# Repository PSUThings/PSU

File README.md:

Both designs work without issue on my end, BOM and Gerbers are there along with Eagle files.  
I have included as much info as i think you will need to get one of these up and running without issue.   
The rear adapters are stl files ready for 3d printing, the original design files i couldnt find, but shouldnt be needed.  
No licence, do what you want with the files.   

As suggested by someone, here is the links to oshpark. These should be easier for people who have no idea how to get a pcb made but can solder well. 

DreamPSU
https://oshpark.com/shared_projects/REVINxcE

SaturnPSU
https://oshpark.com/shared_projects/gURypobA

<!-- Now i have that out the way. Here is a little rant for you that checked this file. This shit is what represents just under 2 years of my life, I loved making the Dreamcast version of the psu cause it was new, fun and interesting, i learned so much from doing this, from eagle stuff to taking a labor of love to production and seeing peoples feedback. But the saturn version? I dont think there was one part of the experience that i enjoyed. Which sucks, i really wanted to do the saturn version cause of peoples constant asking for it, emails, tweets, facebook messages, all the time, so i was totally down to do it. But my god what a fucking shit show its turned out to be. From the mess that is saturn revisions to the fucking absolute disgrace that was the indiegogo campaign. There are god knows how many saturn revisions, which i had to try and source hardware for, which by the way is not an easy feat when your relying on ebay pictures to try and work out if you already own that version of the console, let alone the price of those things, most of which i brought non working or "untested", they cost me between £20-30 each, and i have no use for them after the final design was done. I dont play the saturn and when i did play it as a kid i wasnt a fan of it to be honest. My love was always the PS1 and the dreamcast. The fuck fest that happened with the campaign was nothing but a nightmare, from the first time the manafacturer screwed me over by increasing a quote by almost 30%, to issues with the cabling design for the top doown saturns and chinas inability to follow basic instructions, to the issues with fake or cloned TI chips. i couldnt beleive it. When i was oriignaly considering the saturn and wether or not i should go ahead and do a campaign for it (which by the way i had to, i know people are like "well what about the money you made from the dreampsu campaign", that dreampsu campaign left me damn near 2k in debt. so there was no money to put towards the saturn stuff besides a few intiial prototypes) i never would have dreamed it would turn out the way it did. I let myself down, everyone who help with the campaign down and everyone who made an order elsewhere down. That shit is not easy to handle when your as mentally fucked as i am lmao. And if your wondering, i dont care if i come across as weird or fucked up here, im drunk and im tired and pissed off, let me rant. Talking of ranting, its SOOOO hard to be nice to people all the time when they are berating you and trying to make you feel like shit (which btw guys, good luck cause i already feel as shit as its humanily possible), I do not envy people in customer service jobs.  OK im probably gonna leave this now before i start rambling, but i will say this, to anyone who has a neat idea or something that will help out the retro community, run at it with full force, make it the best thing you can possibly make it and then for the love of god dont try to sell it to anyone. Release that shit open source and never have to go though the same shit i have with this. I do want to say, once again to everyone that backed this thing, i am sorry from the bottom of my heart, this shit rips me apart every damn day knowing that you guys didnt get what u wanted. Hell i fear checking my phone or emails anytime it makes a noise though fear i have to face one of you again. I would also like to say thank you to everyone that was understanding of the sitation, everyone who offered help or guidance and advice, i cannot thank you enough, i dont want to mention people by names cause that aint fair, but you know who you are, even i replied to your email with not very much in the way of words, or didnt reply at all, i read every single email and bit of adcive you sent and i thank you for that.   Thats it from be folks, If at any point i decide to do another PSU for another console, i wont be selling them in any way shape or form, but i will make the files avaible for people as a further apology to everyone for all that has happened.  -->

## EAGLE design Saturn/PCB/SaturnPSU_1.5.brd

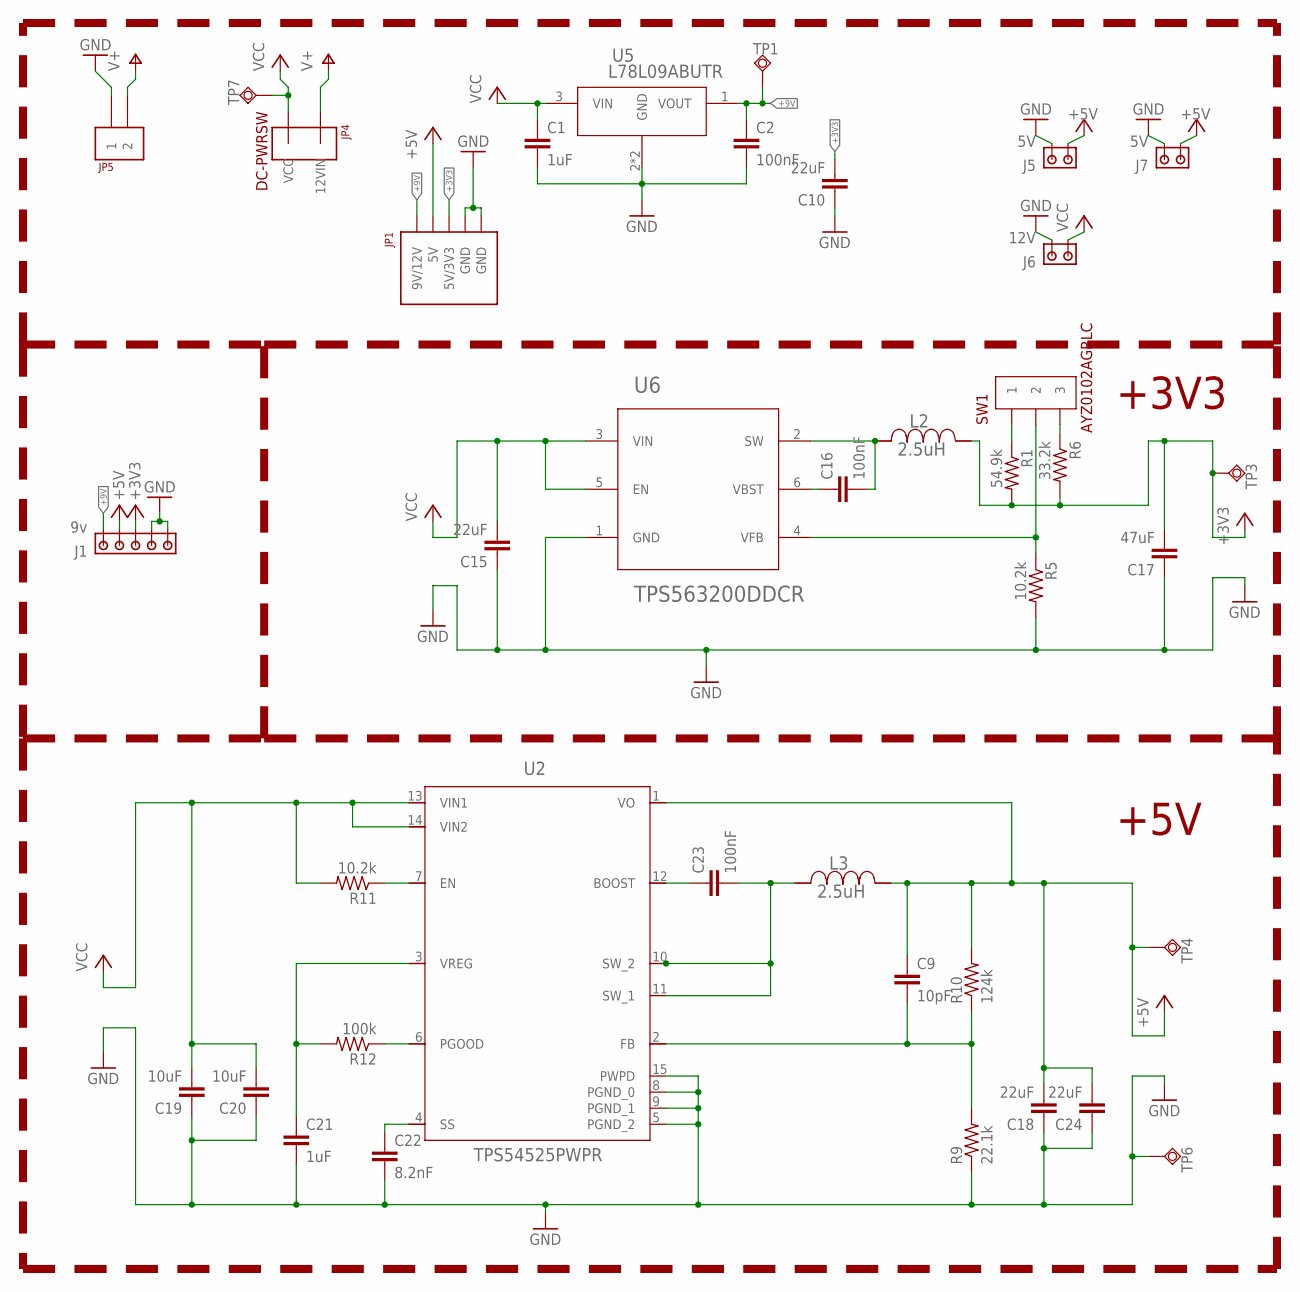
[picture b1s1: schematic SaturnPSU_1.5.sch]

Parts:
C1, C21: 1uF; C0603
C2, C16, C23: 100nF; C0603
C9: 10pF; C0603
C10, C15, C18, C24: 22uF; C0805
C17: 47uF; C1206
C19, C20: 10uF; C1206
C22: 8.2nF; C0603
J1: 9v; KF2510-5A-2.54MM
J5, J7: 5V; 6030916A
J6: 12V; 6030916A
JP1: MOLEX-5PIN-09-48-3054; 09-48-3054
JP4: DC-PWRSW; 1-1123724-2
JP5: 640445-2_3.96MM-2PIN-HEADER
L2, L3: 2.5uH; PA4341.252NLT
R1: 54.9k; R0603
R5, R11: 10.2k; R0603
R6: 33.2k; R0603
R9: 22.1k; R0603
R10: 124k; R0603
R12: 100k; R0603
SW1: AYZ0102AGRLC
TP1, TP3, TP4, TP6, TP7: TPSQB1,27; B1,27
U2: TPS54525PWPR; R-PDSO-G14
U5: L78L09ABUTR; SOT-89
U6: TPS563200DDCR; DDC0006A

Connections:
2: C23.2, L3.P$1 (1), U2.10 (SW_2), U2.11 (SW_1)
+3V3: C10.2, C17.2, J1.3, JP1.3 (5V/3V3), L2.P$2 (2), R1.2, R6.2, TP3.TP
+5V: C9.1, C18.2, C24.2, J1.4, J5.POWER, J7.POWER, JP1.4 (5V), L3.P$2 (2), R10.2, TP4.TP, U2.1 (VO)
+9V: C2.1, J1.5, JP1.5 (9V/12V), TP1.TP, U5.1 (VOUT)
GND: C1.2, C2.2, C10.1, C15.1, C17.1, C18.1, C19.1, C20.1, C21.2, C22.2, C24.1, J1.1, J1.2, J5.GND, J6.GND, J7.GND, JP1.1 (GND), JP1.2 (GND), JP5.P$1 (1), R5.2, R9.1, TP6.TP, U2.5 (PGND_2), U2.8 (PGND_0), U2.9 (PGND_1), U2.15 (PWPD), U5.2 (GND), U5.P$1 (GND), U6.1 (GND)
unnamed: R1.1, SW1.1
unnamed: R6.1, SW1.3
unnamed: C16.2, L2.P$1 (1), U6.2 (SW)
unnamed: C16.1, U6.6 (VBST)
unnamed: R5.1, SW1.2, U6.4 (VFB)
unnamed: R11.1, U2.7 (EN)
unnamed: C21.1, R12.2, U2.3 (VREG)
unnamed: R12.1, U2.6 (PGOOD)
unnamed: C22.1, U2.4 (SS)
unnamed: C9.2, R9.2, R10.1, U2.2 (FB)
unnamed: C23.1, U2.12 (BOOST)
V+: JP4.12VIN, JP5.P$2 (2)
VCC: C1.1, C15.2, C19.2, C20.2, J6.POWER, JP4.VCC, R11.2, TP7.TP, U2.13 (VIN1), U2.14 (VIN2), U5.3 (VIN), U6.3 (VIN), U6.5 (EN)

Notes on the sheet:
+3V3
+5V

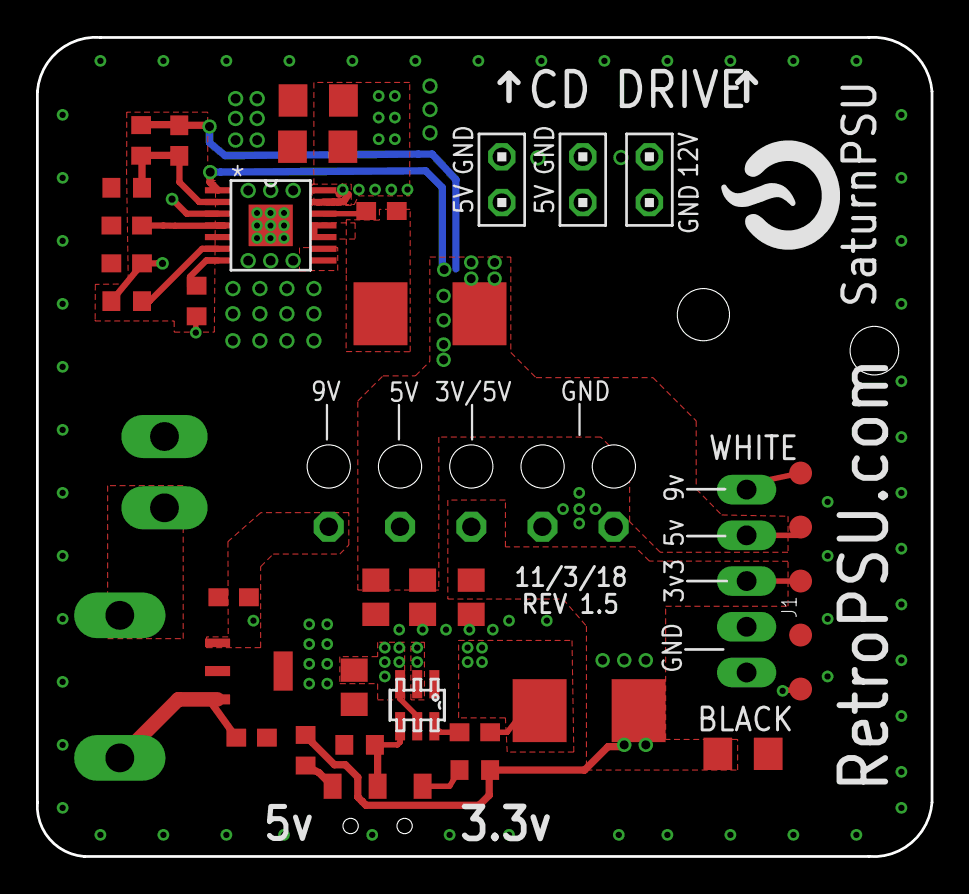
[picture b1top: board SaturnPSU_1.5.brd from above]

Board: 4 copper layers, 49.7 x 45.5 mm, 39 parts (0 on the bottom side), 18 nets.

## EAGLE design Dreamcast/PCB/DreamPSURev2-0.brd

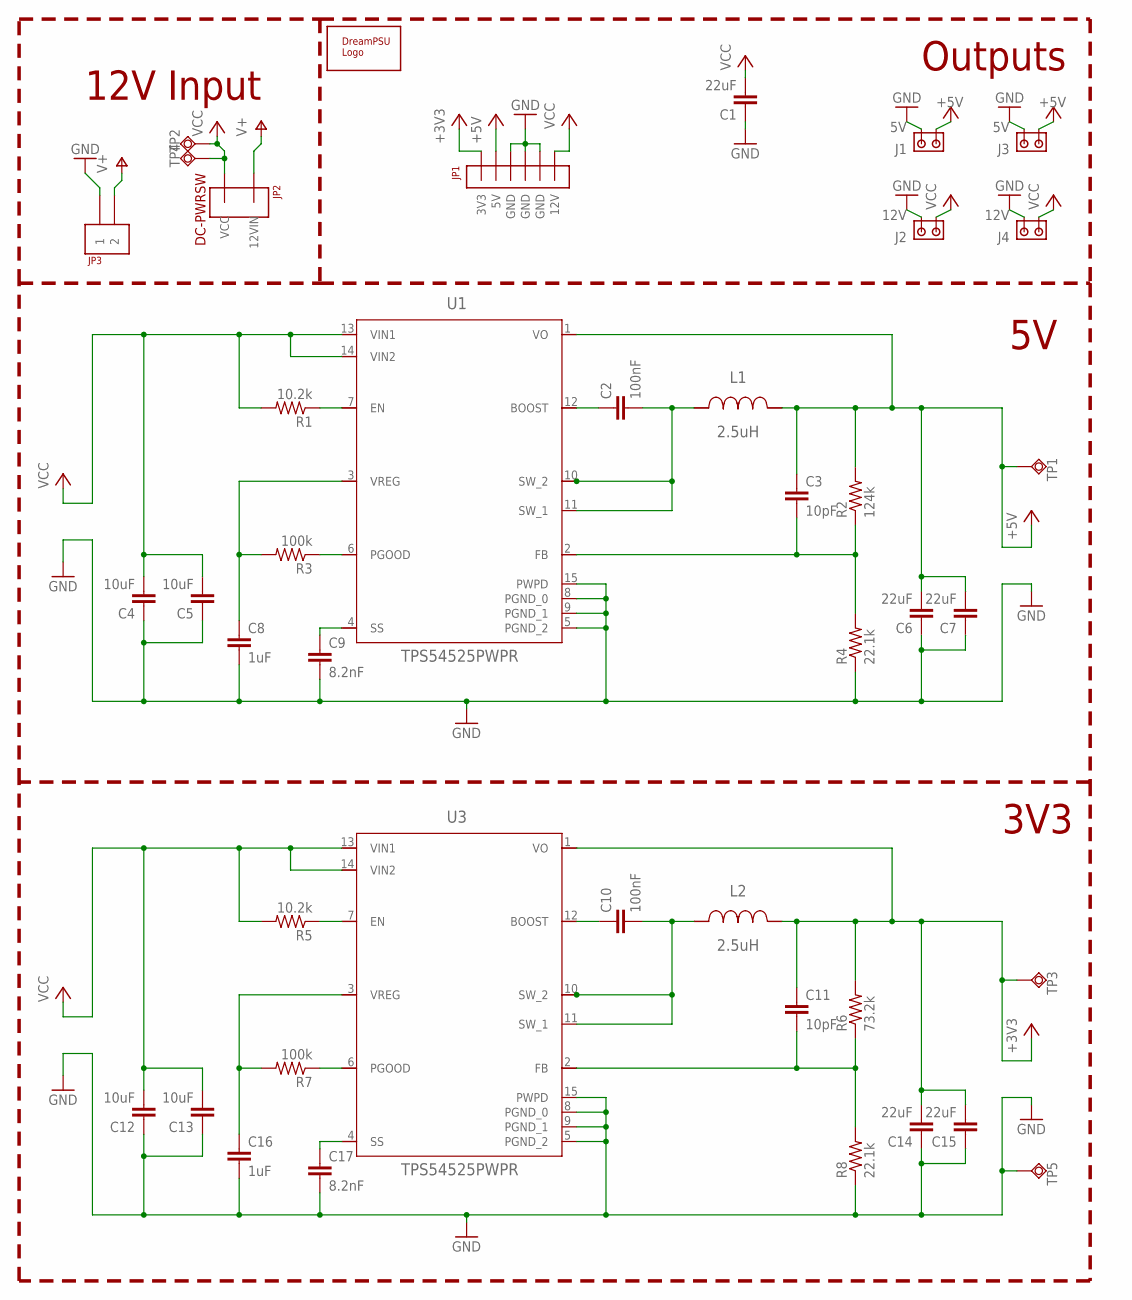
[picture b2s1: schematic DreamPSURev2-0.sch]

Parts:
C1, C6, C7, C14, C15: 22uF; C0805
C2, C10: 100nF; C0603
C3, C11: 10pF; C0603
C4, C5, C12, C13: 10uF; C1206
C8, C16: 1uF; C0603
C9, C17: 8.2nF; C0603
J1, J3: 5V; 10X02MTA
J2, J4: 12V; 10X02MTA
JP1: 09-48-3064; 09-62-3062
JP2: DC-PWRSW; 1-1123724-2
JP3: 640445-2_3.96MM-2PIN-HEADER
L1, L2: 2.5uH; PA4341.252NLT
R1, R5: 10.2k; R0603
R2: 124k; R0603
R3, R7: 100k; R0603
R4, R8: 22.1k; R0603
R6: 73.2k; R0603
TP1, TP2, TP3, TP4, TP5: TPSQB1,27; B1,27
U1, U3: TPS54525PWPR; R-PDSO-G14
U$3: DREAMPSU

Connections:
2: C2.2, L1.P$1 (1), U1.10 (SW_2), U1.11 (SW_1)
18: C10.2, L2.P$1 (1), U3.10 (SW_2), U3.11 (SW_1)
+3V3: C11.1, C14.2, C15.2, JP1.3V3, L2.P$2 (2), R6.2, TP3.TP, U3.1 (VO)
+5V: C3.1, C6.2, C7.2, J1.POWER, J3.POWER, JP1.5V, L1.P$2 (2), R2.2, TP1.TP, U1.1 (VO)
GND: C1.1, C4.1, C5.1, C6.1, C7.1, C8.2, C9.2, C12.1, C13.1, C14.1, C15.1, C16.2, C17.2, J1.GND, J2.GND, J3.GND, J4.GND, JP1.GND@0 (GND), JP1.GND@1 (GND), JP1.GND@2 (GND), JP3.P$1 (1), R4.1, R8.1, TP5.TP, U1.5 (PGND_2), U1.8 (PGND_0), U1.9 (PGND_1), U1.15 (PWPD), U3.5 (PGND_2), U3.8 (PGND_0), U3.9 (PGND_1), U3.15 (PWPD)
unnamed: R1.1, U1.7 (EN)
unnamed: C8.1, R3.2, U1.3 (VREG)
unnamed: R5.1, U3.7 (EN)
unnamed: C10.1, U3.12 (BOOST)
unnamed: R3.1, U1.6 (PGOOD)
unnamed: C9.1, U1.4 (SS)
unnamed: C16.1, R7.2, U3.3 (VREG)
unnamed: R7.1, U3.6 (PGOOD)
unnamed: C17.1, U3.4 (SS)
unnamed: C11.2, R6.1, R8.2, U3.2 (FB)
unnamed: C3.2, R2.1, R4.2, U1.2 (FB)
unnamed: C2.1, U1.12 (BOOST)
V+: JP2.12VIN, JP3.P$2 (2)
VCC: C1.2, C4.2, C5.2, C12.2, C13.2, J2.POWER, J4.POWER, JP1.12V, JP2.VCC, R1.2, R5.2, TP2.TP, TP4.TP, U1.13 (VIN1), U1.14 (VIN2), U3.13 (VIN1), U3.14 (VIN2)

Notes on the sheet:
3V3
Outputs
12V Input

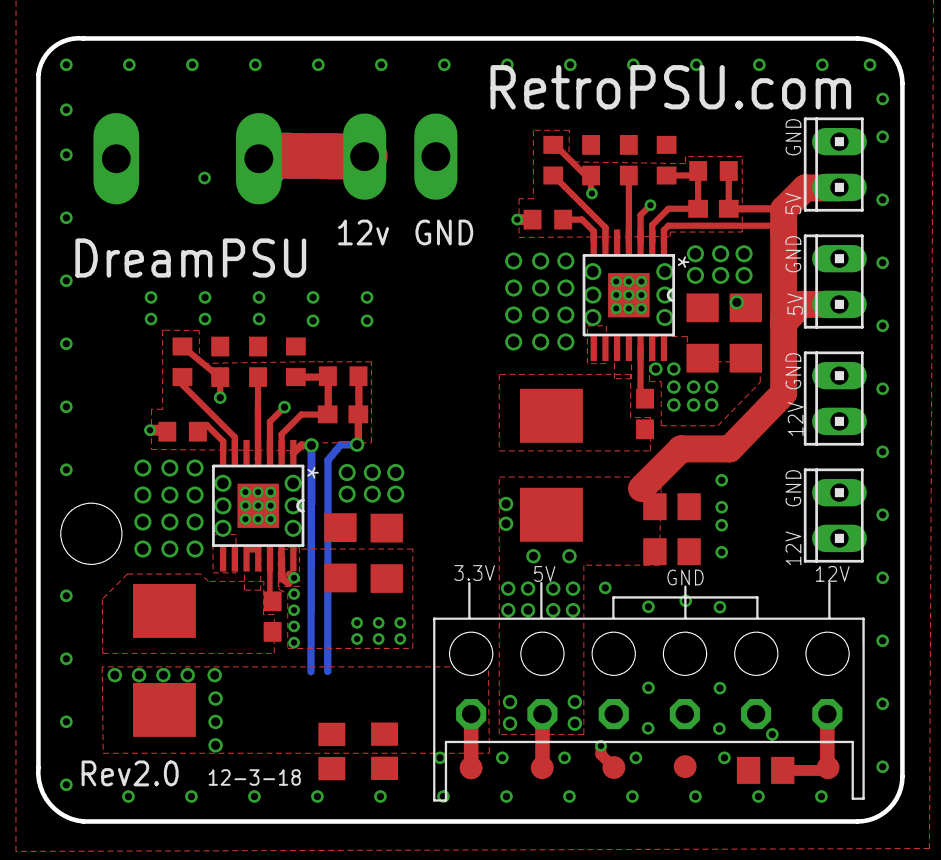
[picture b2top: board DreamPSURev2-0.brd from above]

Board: 4 copper layers, 48.0 x 43.5 mm, 42 parts (1 on the bottom side), 19 nets.

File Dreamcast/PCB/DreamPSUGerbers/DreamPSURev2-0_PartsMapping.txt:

Partlist

Exported from DreamPSURev2-0.brd at 12/03/2018 16:44

EAGLE Version 8.4.3 Copyright (c) 1988-2017 Autodesk, Inc.

Assembly variant: 

Part     Value                       Package                     Library        Position (mm)         Orientation

C1       22uF                        C0805                       DreamPSURev1-9 (39.9 1.84)           R0
C2       100nF                       C0603                       DreamPSURev1-9 (33.2 21.64)          R270
C3       10pF                        C0603                       DreamPSURev1-9 (37 33.04)            R180
C4       10uF                        C1206                       DreamPSURev1-9 (38.8 26.14)          R270
C5       10uF                        C1206                       DreamPSURev1-9 (36.4 26.14)          R270
C6       22uF                        C0805                       DreamPSURev1-9 (34.7 13.99)          R180
C7       22uF                        C0805                       DreamPSURev1-9 (34.7 16.49)          R180
C8       1uF                         C0603                       DreamPSURev1-9 (30.2 35.74)          R90
C9       8.2nF                       C0603                       DreamPSURev1-9 (32.3 35.74)          R90
C10      100nF                       C0603                       DreamPSURev1-9 (12.509 10.385)       R270
C11      10pF                        C0603                       DreamPSURev1-9 (16.42 21.62)         R180
C12      10uF                        C1206                       DreamPSURev1-9 (18.85 13.9)          R270
C13      10uF                        C1206                       DreamPSURev1-9 (16.28 13.93)         R270
C14      22uF                        C0805                       DreamPSURev1-9 (18.7291 2.9035)      R90
C15      22uF                        C0805                       DreamPSURev1-9 (15.8 2.89)           R90
C16      1uF                         C0603                       DreamPSURev1-9 (9.6 24.54)           R90
C17      8.2nF                       C0603                       DreamPSURev1-9 (11.7 24.54)          R90
J1       5V                          10X02MTA                    DreamPSURev1-9 (44 29)               R90
J2       12V                         10X02MTA                    DreamPSURev1-9 (44 22.5)             R90
J3       5V                          10X02MTA                    DreamPSURev1-9 (44 35.5)             R90
J4       12V                         10X02MTA                    DreamPSURev1-9 (44 16)               R90
JP1      09-48-3064                  09-62-3062                  DreamPSURev1-9 (33.44 8.32)          R0
JP2      DC-PWRSW                    1-1123724-2                 SaturnPSU_1.5  (7.786 35.823)        R180
JP3      640445-2_3.96MM-2PIN-HEADER 640445-2_3.96MM-2PIN-HEADER SaturnPSU_1.5  (19.6 35.94)          R180
L1       2.5uH                       PA4341.252NLT               SaturnPSU_1.5  (28 19.04)            R0
L2       2.5uH                       PA4341.252NLT               SaturnPSU_1.5  (6.5 8.2)             R0
R1       10.2k                       R0603                       DreamPSURev1-9 (27.8 32.44)          R180
R2       124k                        R0603                       DreamPSURev1-9 (37 35.14)            R0
R3       100k                        R0603                       DreamPSURev1-9 (28.1 35.74)          R90
R4       22.1k                       R0603                       DreamPSURev1-9 (34.4 35.74)          R270
R5       10.2k                       R0603                       DreamPSURev1-9 (7.508 20.657)        R180
R6       73.2k                       R0603                       DreamPSURev1-9 (16.43 23.739)        R0
R7       100k                        R0603                       DreamPSURev1-9 (7.5 24.54)           R90
R8       22.1k                       R0603                       DreamPSURev1-9 (13.8 24.54)          R270
TP1      TPSQB1,27                   B1,27                       DreamPSURev1-9 (27.49 1.99)          R0
TP2      TPSQB1,27                   B1,27                       DreamPSURev1-9 (31.47 2)             R0
TP3      TPSQB1,27                   B1,27                       DreamPSURev1-9 (23.5352 1.9785)      R0
TP4      TPSQB1,27                   B1,27                       DreamPSURev1-9 (43.37 1.99)          R0
TP5      TPSQB1,27                   B1,27                       DreamPSURev1-9 (35.43 2.05)          R0
U1       TPS54525PWPR                R-PDSO-G14                  DreamPSURev1-9 (32.3 28.24)          R270
U3       TPS54525PWPR                R-PDSO-G14                  DreamPSURev1-9 (11.71 16.54)         R270

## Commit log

2019-09-12 Create Design flaws
